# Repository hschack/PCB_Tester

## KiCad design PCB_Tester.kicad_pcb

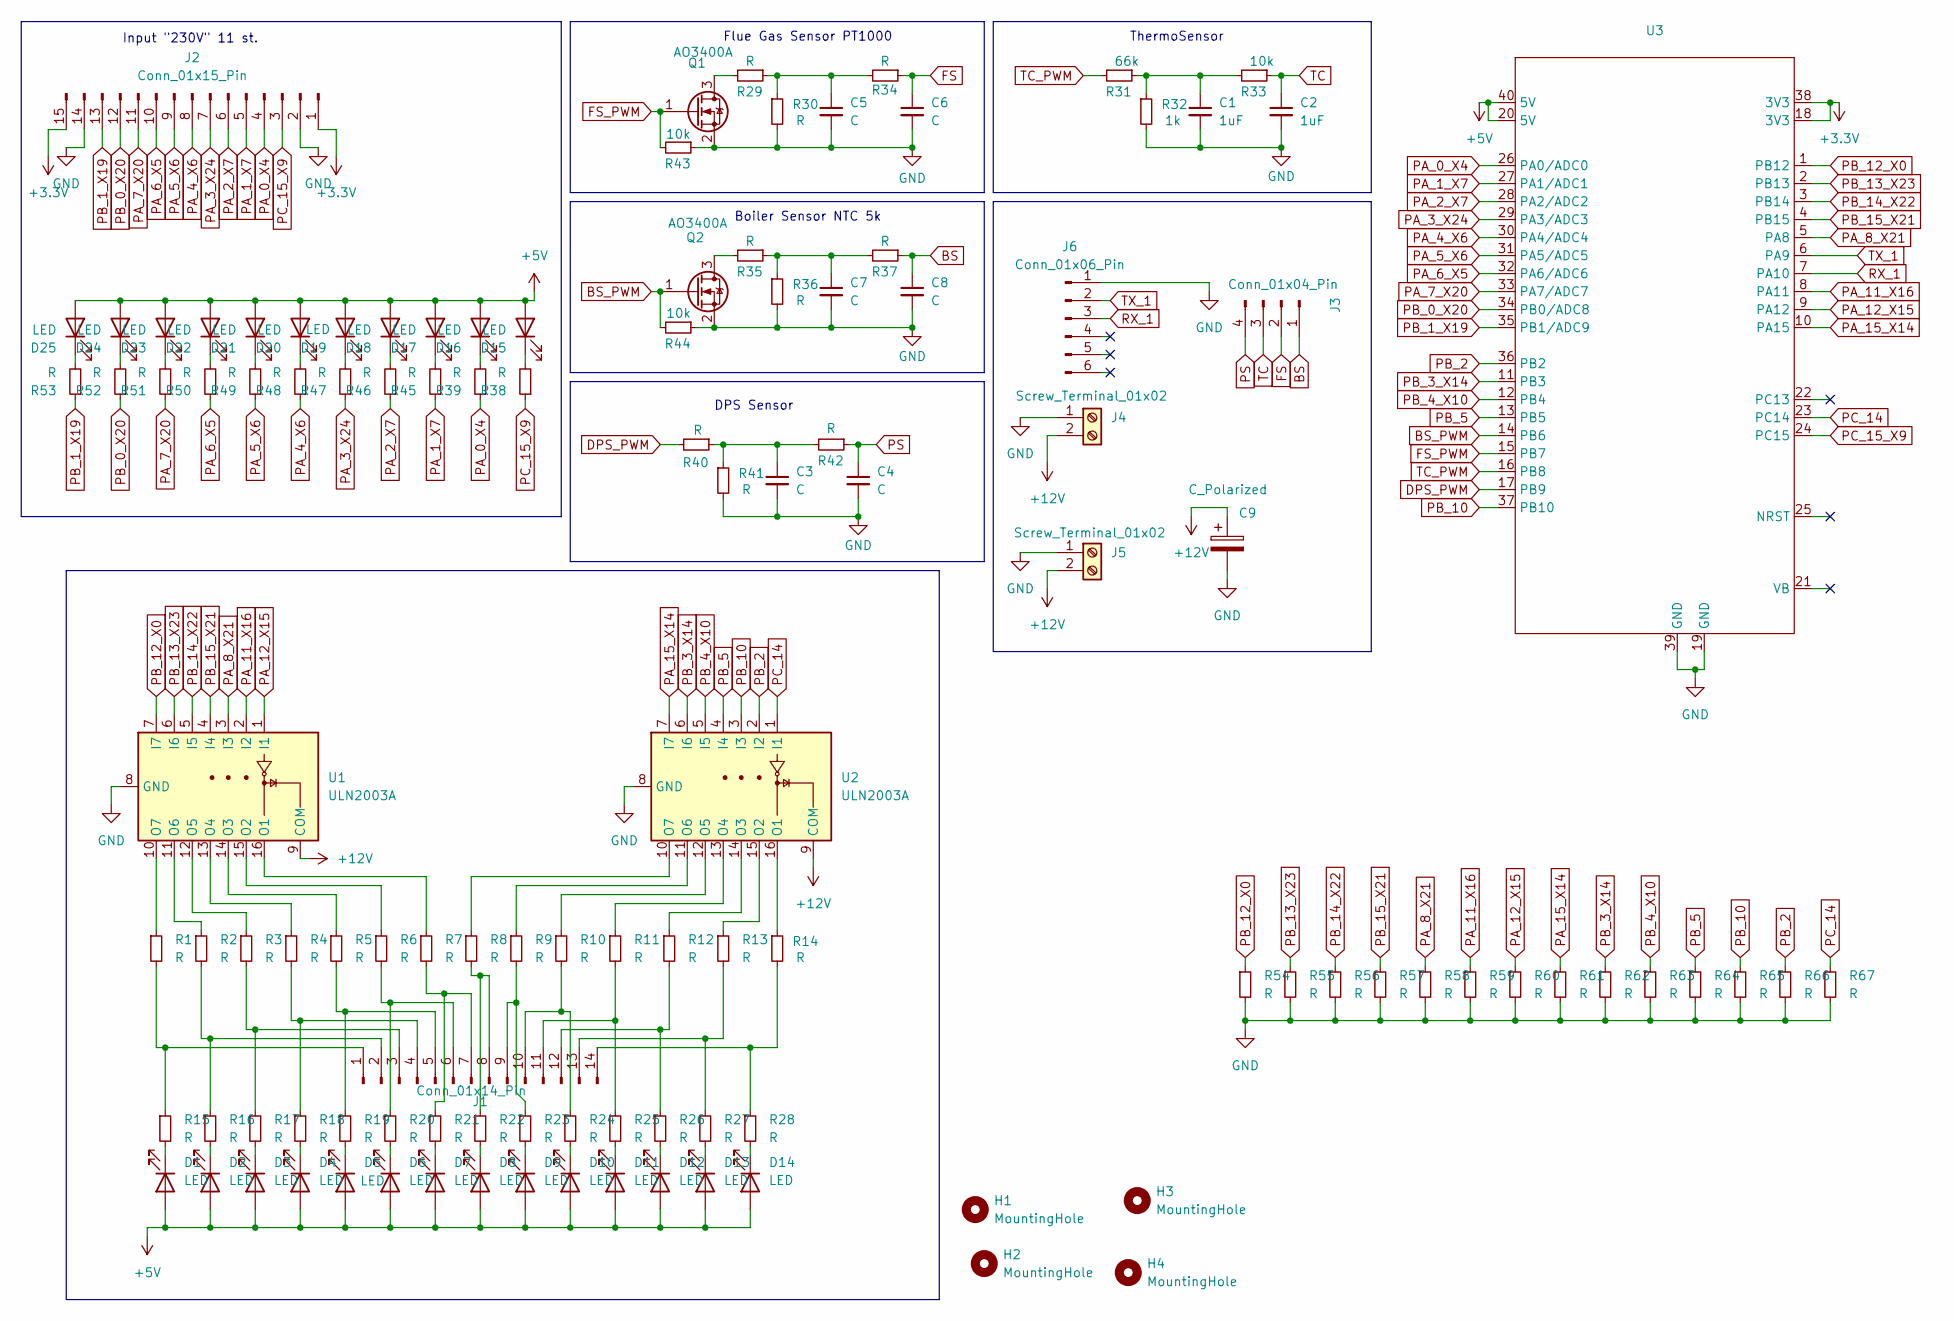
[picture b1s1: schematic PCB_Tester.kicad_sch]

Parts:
C1, C2: 1uF; C_0805_2012Metric
C3, C4, C5, C6, C7, C8: C; C_0805_2012Metric
C9: C_Polarized; CP_Radial_D10.0mm_P5.00mm
D1, D2, D3, D4, D5, D6, D7, D8, D9, D10, D11, D12, D13, D14, D15, D16, D17, D18, D19, D20, D21, D22, D23, D24, D25: LED; LED_0805_2012Metric
H1, H2, H3, H4: MountingHole; MountingHole_3.2mm_M3
J1: Conn_01x14_Pin; PinHeader_1x14_P2.54mm_Vertical
J2: Conn_01x15_Pin; PinHeader_1x15_P2.54mm_Vertical
J3: Conn_01x04_Pin; PinHeader_1x04_P2.54mm_Vertical
J4, J5: Screw_Terminal_01x02; PhoenixContact_MCV_1,5_2-G-3.5_1x02_P3.50mm_Vertical
J6: Conn_01x06_Pin; PinHeader_1x06_P2.54mm_Vertical
Q1, Q2: AO3400A; SOT-23
R1, R2, R3, R4, R5, R6, R7, R8, R9, R10, R11, R12, R13, R14, R15, R16, R17, R18, R19, R20, R21, R22, R23, R24, R25, R26, R27, R28, R29, R30, R34, R35, R36, R37, R38, R39, R40, R41, R42, R45, R46, R47, R48, R49, R50, R51, R52, R53, R54, R55, R56, R57, R58, R59, R60, R61, R62, R63, R64, R65, R66, R67: R; R_0805_2012Metric
R31: 66k; R_0805_2012Metric
R32: 1k; R_0805_2012Metric
R33, R43, R44: 10k; R_0805_2012Metric
U1, U2: ULN2003A; DIP-16_W7.62mm_Socket
U3: DIP-40_W15.24mm_Socket

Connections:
+3.3V: J2.1, J2.15, U3.18 (3V3), U3.38 (3V3)
+5V: D1.2 (A), D2.2 (A), D3.2 (A), D4.2 (A), D5.2 (A), D6.2 (A), D7.2 (A), D8.2 (A), D9.2 (A), D10.2 (A), D11.2 (A), D12.2 (A), D13.2 (A), D14.2 (A), D15.2 (A), D16.2 (A), D17.2 (A), D18.2 (A), D19.2 (A), D20.2 (A), D21.2 (A), D22.2 (A), D23.2 (A), D24.2 (A), D25.2 (A), U3.20 (5V), U3.40 (5V)
+12V: C9.1, J4.2, J5.2, U1.9 (COM), U2.9 (COM)
BS: C8.1, J3.1, R37.1
BS_PWM: Q2.1 (G), R44.2, U3.14 (PB6)
DPS_PWM: R40.2, U3.17 (PB9)
FS: C6.1, J3.2, R34.1
FS_PWM: Q1.1 (G), R43.2, U3.15 (PB7)
GND: C1.2, C2.2, C3.2, C4.2, C5.2, C6.2, C7.2, C8.2, C9.2, J2.2, J2.14, J4.1, J5.1, J6.1, Q1.2 (S), Q2.2 (S), R30.2, R32.2, R36.2, R41.2, R43.1, R44.1, R54.2, R55.2, R56.2, R57.2, R58.2, R59.2, R60.2, R61.2, R62.2, R63.2, R64.2, R65.2, R66.2, R67.2, U1.8 (GND), U2.8 (GND), U3.19 (GND), U3.39 (GND)
unnamed: C1.1, R31.1, R32.1, R33.2
unnamed: C3.1, R40.1, R41.1, R42.2
unnamed: C5.1, R29.1, R30.1, R34.2
unnamed: C7.1, R35.1, R36.1, R37.2
unnamed: D1.1 (K), R15.2
unnamed: D2.1 (K), R16.2
unnamed: D3.1 (K), R17.2
unnamed: D4.1 (K), R18.2
unnamed: D5.1 (K), R19.2
unnamed: D6.1 (K), R20.2
unnamed: D7.1 (K), R21.2
unnamed: D8.1 (K), R22.2
unnamed: D9.1 (K), R23.2
unnamed: D10.1 (K), R24.2
unnamed: D11.1 (K), R25.2
unnamed: D12.1 (K), R26.2
unnamed: D13.1 (K), R27.2
unnamed: D14.1 (K), R28.2
unnamed: D15.1 (K), R38.2
unnamed: D16.1 (K), R39.2
unnamed: D17.1 (K), R45.2
unnamed: D18.1 (K), R46.2
unnamed: D19.1 (K), R47.2
unnamed: D20.1 (K), R48.2
unnamed: D21.1 (K), R49.2
unnamed: D22.1 (K), R50.2
unnamed: D23.1 (K), R51.2
unnamed: D24.1 (K), R52.2
unnamed: D25.1 (K), R53.2
unnamed: J1.1, R1.2, R15.1
unnamed: J1.2, R2.2, R16.1
unnamed: J1.3, R3.2, R17.1
unnamed: J1.4, R4.2, R18.1
unnamed: J1.5, R5.2, R19.1
unnamed: J1.6, R6.2, R20.1
unnamed: J1.7, R7.2, R21.1
unnamed: J1.8, R8.2, R22.1
unnamed: J1.9, R9.2, R23.1
unnamed: J1.10, R10.2, R24.1
unnamed: J1.11, R11.2, R25.1
unnamed: J1.12, R12.2, R26.1
unnamed: J1.13, R13.2, R27.1
unnamed: J1.14, R14.2, R28.1
unnamed: Q1.3 (D), R29.2
unnamed: Q2.3 (D), R35.2
unnamed: R7.1, U1.16 (O1)
unnamed: R6.1, U1.15 (O2)
unnamed: R5.1, U1.14 (O3)
unnamed: R4.1, U1.13 (O4)
unnamed: R3.1, U1.12 (O5)
unnamed: R2.1, U1.11 (O6)
unnamed: R1.1, U1.10 (O7)
unnamed: R14.1, U2.16 (O1)
unnamed: R13.1, U2.15 (O2)
unnamed: R12.1, U2.14 (O3)
unnamed: R11.1, U2.13 (O4)
unnamed: R10.1, U2.12 (O5)
unnamed: R9.1, U2.11 (O6)
unnamed: R8.1, U2.10 (O7)
PA_0_X4: J2.4, R39.1, U3.26 (PA0/ADC0)
PA_1_X7: J2.5, R45.1, U3.27 (PA1/ADC1)
PA_2_X7: J2.6, R46.1, U3.28 (PA2/ADC2)
PA_3_X24: J2.7, R47.1, U3.29 (PA3/ADC3)
PA_4_X6: J2.8, R48.1, U3.30 (PA4/ADC4)
PA_5_X6: J2.9, R49.1, U3.31 (PA5/ADC5)
PA_6_X5: J2.10, R50.1, U3.32 (PA6/ADC6)
PA_7_X20: J2.11, R51.1, U3.33 (PA7/ADC7)
PA_8_X21: R58.1, U1.3 (I3), U3.5 (PA8)
PA_11_X16: R59.1, U1.2 (I2), U3.8 (PA11)
PA_12_X15: R60.1, U1.1 (I1), U3.9 (PA12)
PA_15_X14: R61.1, U2.7 (I7), U3.10 (PA15)
PB_0_X20: J2.12, R52.1, U3.34 (PB0/ADC8)
PB_1_X19: J2.13, R53.1, U3.35 (PB1/ADC9)
PB_2: R66.1, U2.2 (I2), U3.36 (PB2)
PB_3_X14: R62.1, U2.6 (I6), U3.11 (PB3)
PB_4_X10: R63.1, U2.5 (I5), U3.12 (PB4)
PB_5: R64.1, U2.4 (I4), U3.13 (PB5)
PB_10: R65.1, U2.3 (I3), U3.37 (PB10)
PB_12_X0: R54.1, U1.7 (I7), U3.1 (PB12)
PB_13_X23: R55.1, U1.6 (I6), U3.2 (PB13)
PB_14_X22: R56.1, U1.5 (I5), U3.3 (PB14)
PB_15_X21: R57.1, U1.4 (I4), U3.4 (PB15)
PC_14: R67.1, U2.1 (I1), U3.23 (PC14)
PC_15_X9: J2.3, R38.1, U3.24 (PC15)
PS: C4.1, J3.4, R42.1
RX_1: J6.3, U3.7 (PA10)
TC: C2.1, J3.3, R33.1
TC_PWM: R31.2, U3.16 (PB8)
TX_1: J6.2, U3.6 (PA9)

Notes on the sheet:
Boiler Sensor NTC 5k
DPS Sensor
ThermoSensor
Flue Gas Sensor PT1000
Input "230V" 11 st.

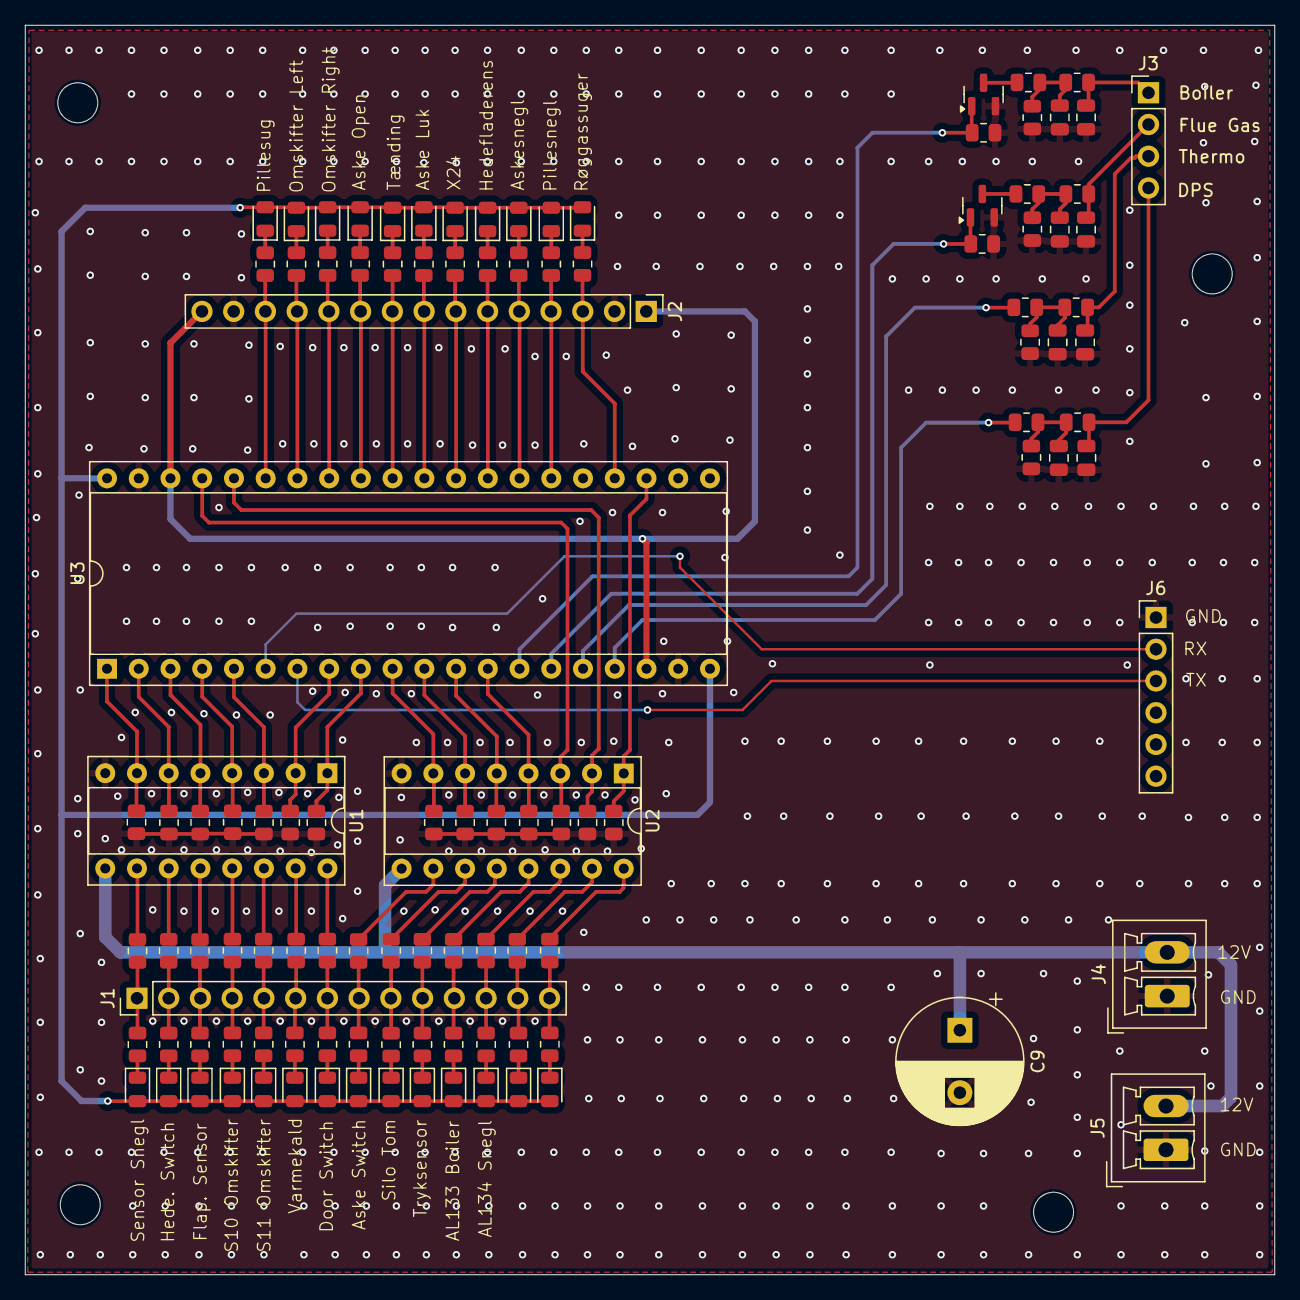
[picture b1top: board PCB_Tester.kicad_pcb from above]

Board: 2 copper layers, 100.0 x 100.0 mm, 116 parts (0 on the bottom side), 98 nets.

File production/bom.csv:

Designator,Footprint,Quantity,Value,LCSC Part #
"C1, C2",0805,2,1uF,
"C3, C4, C5, C6, C7, C8",0805,6,C,
C9,CP_Radial_D10.0mm_P5.00mm,1,C_Polarized,
"D1, D10, D11, D12, D13, D14, D15, D16, D17, D18, D19, D2, D20, D21, D22, D23, D24, D25, D3, D4, D5, D6, D7, D8, D9",0805,25,LED,
J1,PinHeader_1x14_P2.54mm_Vertical,1,Conn_01x14_Pin,
J2,PinHeader_1x15_P2.54mm_Vertical,1,Conn_01x15_Pin,
J3,PinHeader_1x04_P2.54mm_Vertical,1,Conn_01x04_Pin,
"J4, J5","PhoenixContact_MCV_1,5_2-G-3.5_1x02_P3.50mm_Vertical",2,Screw_Terminal_01x02,
J6,PinHeader_1x06_P2.54mm_Vertical,1,Conn_01x06_Pin,
"Q1, Q2",SOT-23,2,AO3400A,
"R1, R10, R11, R12, R13, R14, R15, R16, R17, R18, R19, R2, R20, R21, R22, R23, R24, R25, R26, R27, R28, R29, R3, R30, R34, R35, R36, R37, R38, R39, R4, R40, R41, R42, R45, R46, R47, R48, R49, R5, R50, R51, R52, R53, R54, R55, R56, R57, R58, R59, R6, R60, R61, R62, R63, R64, R65, R66, R67, R7, R8, R9",0805,62,R,
R31,0805,1,66k,
R32,0805,1,1k,
"R33, R43, R44",0805,3,10k,
"U1, U2",DIP-16_W7.62mm_Socket,2,ULN2003A,
U3,DIP-40_W15.24mm_Socket,1,~,
